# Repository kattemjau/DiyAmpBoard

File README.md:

# DiyAmpBoard
Diy amplifier breakout

Made in kicad

Made arround Tpa3116
http://www.farnell.com/datasheets/1813458.pdf

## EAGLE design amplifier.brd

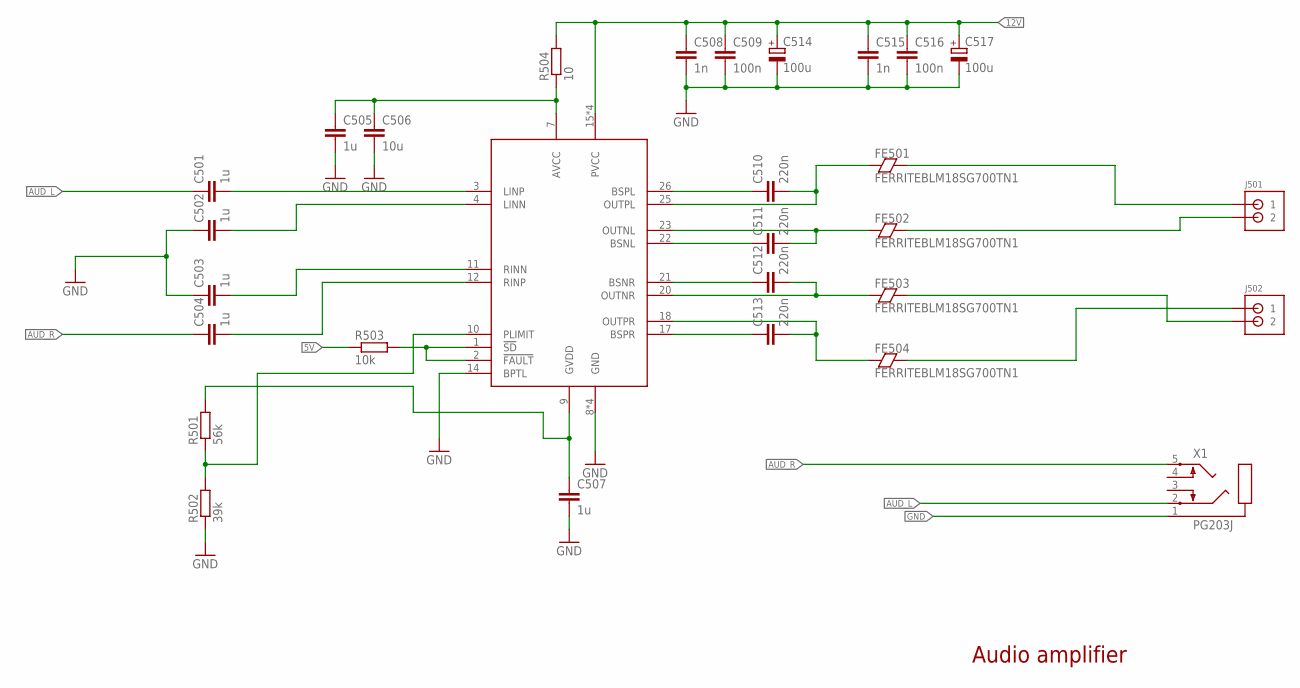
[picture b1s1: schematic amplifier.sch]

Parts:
C501, C502, C503, C504, C505, C507: 1u; C0603
C506: 10u; C0603
C508, C515: 1n; C0603
C509, C516: 100n; C0603
C510, C511, C512, C513: 220n; C0603
C514, C517: 100u; CAP6.6X8
FE501, FE502, FE503, FE504: FERRITEBLM18SG700TN1; R0603
J501, J502: CONNECTOR-2JST-XH-2; JST-XH-2
R501: 56k; R0603
R502: 39k; R0603
R503: 10k; R0603
R504: 10; R0603
U501: TPA3136D2; R-PDSO-G28
X1: PG203J

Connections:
5V: R503.1
12V: C508.1, C509.1, C514.1 (+), C515.1, C516.1, C517.1 (+), R504.2, U501.15 (PVCC), U501.16 (PVCC), U501.27 (PVCC), U501.28 (PVCC)
AUD_L: C501.1, X1.2
AUD_R: C504.1, X1.5
GND: C502.1, C503.1, C505.2, C506.2, C507.2, C508.2, C509.2, C514.2 (-), C515.2, C516.2, C517.2 (-), R502.1, U501.8 (GND), U501.14 (BPTL), U501.19 (GND), U501.24 (GND), U501.POWER (GND), X1.1
unnamed: C501.2, U501.3 (LINP)
unnamed: C502.2, U501.4 (LINN)
unnamed: C503.2, U501.11 (RINN)
unnamed: C504.2, U501.12 (RINP)
unnamed: C512.1, U501.21 (BSNR)
unnamed: C513.1, U501.17 (BSPR)
unnamed: C511.1, U501.22 (BSNL)
unnamed: C510.1, U501.26 (BSPL)
unnamed: C510.2, FE501.1, U501.25 (OUTPL)
unnamed: C511.2, FE502.1, U501.23 (OUTNL)
unnamed: C512.2, FE503.1, U501.20 (OUTNR)
unnamed: C513.2, FE504.1, U501.18 (OUTPR)
unnamed: FE502.2, J501.P2 (2)
unnamed: FE501.2, J501.P1 (1)
unnamed: FE503.2, J502.P2 (2)
unnamed: FE504.2, J502.P1 (1)
unnamed: C507.1, R501.2, U501.9 (GVDD)
unnamed: R503.2, U501.1 (!SD), U501.2 (!FAULT)
unnamed: C505.1, C506.1, R504.1, U501.7 (AVCC)
unnamed: R501.1, R502.2, U501.10 (PLIMIT)

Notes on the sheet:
Audio amplifier

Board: 2 copper layers, 29 parts (0 on the bottom side), 24 nets, no tracks yet.

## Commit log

2019-02-27 first upload boi
    schematic 50% done
2019-02-27 added pdf of schematic
2019-03-03 updated ic
2019-03-03 added schematic
